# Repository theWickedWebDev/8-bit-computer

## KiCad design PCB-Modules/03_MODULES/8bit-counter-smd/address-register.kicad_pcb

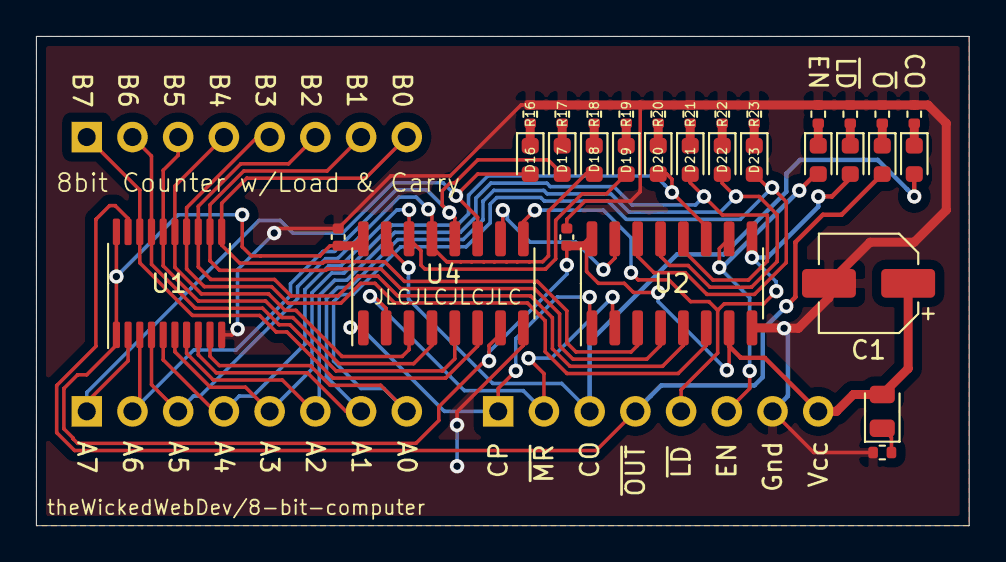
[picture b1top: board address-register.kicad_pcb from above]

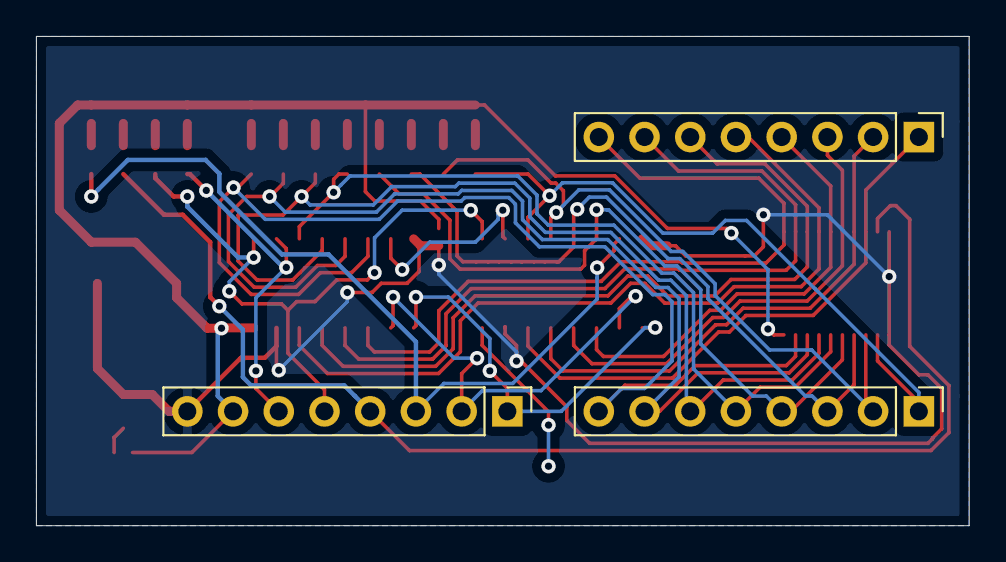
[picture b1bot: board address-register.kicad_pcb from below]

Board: 2 copper layers, 51.8 x 27.2 mm, 35 parts (3 on the bottom side), 38 nets.

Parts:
C1: SMD-ECAP-5x5.8; CP_Elec_5x5.8
C2, C5: CL05A106MQ5NUNC; C_0402_1005Metric
D2, D7, D12: 19-217/BHC-ZL1M2RY/3T; LED_0603_1608Metric
D6: NCD0805R1; LED_0805_2012Metric
D16, D17, D18, D19, D20, D21, D22, D23: 19-217/GHC-YR1S2/3T; LED_0603_1608Metric
J1, J2, J3: Conn_01x08; PinHeader_1x08_P2.54mm_Vertical
R2, R6, R7, R12, R14, R16, R17, R18, R19, R20, R21, R22, R23: 0402WGF1001TCE; R_0402_1005Metric
U1: 74HC245PW,118; TSSOP-20_4.4x6.5mm_P0.65mm
U2, U4: SN74HC161DR; SOIC-16_3.9x9.9mm_P1.27mm
U3: 19-213_Y2C-CQ2R2L_3T(CY); LED_0603_1608Metric

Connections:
BUS_00: J2.8, U1.11, U2.3
BUS_01: J2.7, U1.12, U2.4
BUS_02: J2.6, U1.13, U2.5
BUS_03: J2.5, U1.14, U2.6
BUS_04: J2.4, U1.15, U4.3
BUS_05: J2.3, U1.16, U4.4
BUS_06: J2.2, U1.17, U4.5
BUS_07: J2.1, U1.18, U4.6
CARRY_OUT: J1.3, U3.2, U4.15
CLOCK: J1.2, U2.2, U4.2
EN: D2.2, J1.6, U2.10
GND: C1.2, C2.2, C5.2, J1.7, R2.2, R6.2, R7.2, R12.2, R14.2, R16.2, R17.2, R18.2, R19.2, R20.2, R21.2, R22.2, R23.2, U1.10, U2.8, U4.8
unnamed: D2.1, R2.1
unnamed: D6.1, R6.1
unnamed: D7.1, R7.1
unnamed: D12.1, R12.1
unnamed: D16.1, R16.1
unnamed: D17.1, R17.1
unnamed: D18.1, R18.1
unnamed: D19.1, R19.1
unnamed: D20.1, R20.1
unnamed: D21.1, R21.1
unnamed: D22.1, R22.1
unnamed: D23.1, R23.1
unnamed: R14.1, U3.1
unnamed: U2.15, U4.10
Q0: D23.2, J3.8, U1.9, U2.14
Q1: D22.2, J3.7, U1.8, U2.13
Q2: D21.2, J3.6, U1.7, U2.12
Q3: D20.2, J3.5, U1.6, U2.11
Q4: D19.2, J3.4, U1.5, U4.14
Q5: D18.2, J3.3, U1.4, U4.13
Q6: D17.2, J3.2, U1.3, U4.12
Q7: D16.2, J3.1, U1.2, U4.11
VCC: C1.1, C2.1, C5.1, D6.2, J1.8, U1.1, U1.20, U2.7, U2.16, U4.7, U4.16
~LOAD: D7.2, J1.5, U2.9, U4.9
~OUT: D12.2, J1.4, U1.19
~RESET: J1.1, U2.1, U4.1

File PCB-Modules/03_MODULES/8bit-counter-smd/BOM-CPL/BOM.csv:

Designator,Value,LibPart,Footprint,Datasheet,C,Color,Description,JCLC,JLCPCB,NAME,,
C1,SMD-ECAP-5x5.8,Device:CP1_Small,Capacitor_SMD:CP_Elec_5x5.8,https://datasheet.lcsc.com/lcsc/1810010225_Lelon-VZS101M1ATR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,100µf,,"- - 5mm 100uF 10V -45℃~+105℃ ±20% 5.8mm 2000hrs 105℃ SMD,5x5.8mm Aluminum Electrolytic Capacitors - SMD ROHS",C140924,C140924,,,
C2,CL05A106MQ5NUNC,Device:C,Capacitor_SMD:C_0402_1005Metric,https://datasheet.lcsc.com/lcsc/1810191215_Samsung-Electro-M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,10µf,,X5R 6.3V ±20% 10uF 0402 Multilayer Ceramic Capacitors MLCC - SMD/SMT ROHS,C15525,C15525,,,
C5,CL05A106MQ5NUNC,Device:C,Capacitor_SMD:C_0402_1005Metric,https://datasheet.lcsc.com/lcsc/1810191215_Samsung-Electro-M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,10µf,,X5R 6.3V ±20% 10uF 0402 Multilayer Ceramic Capacitors MLCC - SMD/SMT ROHS,C15525,C15525,,,
D2,19-217/BHC-ZL1M2RY/3T,Device:LED,LED_SMD:LED_0603_1608Metric,https://datasheet.lcsc.com/lcsc/1811101510_Everlight-Elec-19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,,BLU,,C72041,C72041,,,
D6,NCD0805R1,Device:LED,LED_SMD:LED_0805_2012Metric,https://datasheet.lcsc.com/lcsc/2008201032_Foshan-NationStar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,,RED,,,C84256,,,
D7,19-217/BHC-ZL1M2RY/3T,Device:LED,LED_SMD:LED_0603_1608Metric,https://datasheet.lcsc.com/lcsc/1811101510_Everlight-Elec-19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,,BLU,,C72041,C72041,,,
D12,19-217/BHC-ZL1M2RY/3T,Device:LED,LED_SMD:LED_0603_1608Metric,https://datasheet.lcsc.com/lcsc/1811101510_Everlight-Elec-19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,,BLU,,C72041,C72041,,,
D16,19-217/GHC-YR1S2/3T,Device:LED,LED_SMD:LED_0603_1608Metric,https://datasheet.lcsc.com/lcsc/1811101510_Everlight-Elec-19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,,GRN,,C72043,C72043,,,
D17,19-217/GHC-YR1S2/3T,Device:LED,LED_SMD:LED_0603_1608Metric,https://datasheet.lcsc.com/lcsc/1811101510_Everlight-Elec-19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,,GRN,,C72043,C72043,,,
D18,19-217/GHC-YR1S2/3T,Device:LED,LED_SMD:LED_0603_1608Metric,https://datasheet.lcsc.com/lcsc/1811101510_Everlight-Elec-19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,,GRN,,C72043,C72043,,,
D19,19-217/GHC-YR1S2/3T,Device:LED,LED_SMD:LED_0603_1608Metric,https://datasheet.lcsc.com/lcsc/1811101510_Everlight-Elec-19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,,GRN,,C72043,C72043,,,
D20,19-217/GHC-YR1S2/3T,Device:LED,LED_SMD:LED_0603_1608Metric,https://datasheet.lcsc.com/lcsc/1811101510_Everlight-Elec-19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,,GRN,,C72043,C72043,,,
D21,19-217/GHC-YR1S2/3T,Device:LED,LED_SMD:LED_0603_1608Metric,https://datasheet.lcsc.com/lcsc/1811101510_Everlight-Elec-19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,,GRN,,C72043,C72043,,,
D22,19-217/GHC-YR1S2/3T,Device:LED,LED_SMD:LED_0603_1608Metric,https://datasheet.lcsc.com/lcsc/1811101510_Everlight-Elec-19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,,GRN,,C72043,C72043,,,
D23,19-217/GHC-YR1S2/3T,Device:LED,LED_SMD:LED_0603_1608Metric,https://datasheet.lcsc.com/lcsc/1811101510_Everlight-Elec-19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,,GRN,,C72043,C72043,,,
J1,Conn_01x08,Connector_Generic:Conn_01x08,Connector_PinHeader_2.54mm:PinHeader_1x08_P2.54mm_Vertical,~,,,,,,,,
J2,Conn_01x08,Connector_Generic:Conn_01x08,Connector_PinHeader_2.54mm:PinHeader_1x08_P2.54mm_Vertical,~,,,,,,,,
J3,Conn_01x08,Connector_Generic:Conn_01x08,Connector_PinHeader_2.54mm:PinHeader_1x08_P2.54mm_Vertical,~,,,,,,,,
R2,0402WGF1001TCE,Device:R_Small_US,Resistor_SMD:R_0402_1005Metric,https://datasheet.lcsc.com/lcsc/1811132311_UNI-ROYAL-Uniroya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,,,±1% 1/16W ±100ppm/℃ 1kΩ 0402 Chip Resistor - Surface Mount ROHS,C11702,C11702,,,
R6,0402WGF1001TCE,Device:R_Small_US,Resistor_SMD:R_0402_1005Metric,https://datasheet.lcsc.com/lcsc/1811132311_UNI-ROYAL-Uniroya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,,,±1% 1/16W ±100ppm/℃ 1kΩ 0402 Chip Resistor - Surface Mount ROHS,,C11702,,,
R7,0402WGF1001TCE,Device:R_Small_US,Resistor_SMD:R_0402_1005Metric,https://datasheet.lcsc.com/lcsc/1811132311_UNI-ROYAL-Uniroya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,,,±1% 1/16W ±100ppm/℃ 1kΩ 0402 Chip Resistor - Surface Mount ROHS,C11702,C11702,,,
R12,0402WGF1001TCE,Device:R_Small_US,Resistor_SMD:R_0402_1005Metric,https://datasheet.lcsc.com/lcsc/1811132311_UNI-ROYAL-Uniroya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,,,±1% 1/16W ±100ppm/℃ 1kΩ 0402 Chip Resistor - Surface Mount ROHS,C11702,C11702,,,
R14,0402WGF1001TCE,Device:R_Small_US,Resistor_SMD:R_0402_1005Metric,https://datasheet.lcsc.com/lcsc/1811132311_UNI-ROYAL-Uniroya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,,,±1% 1/16W ±100ppm/℃ 1kΩ 0402 Chip Resistor - Surface Mount ROHS,,C11702,,,
R16,0402WGF1001TCE,Device:R_Small_US,Resistor_SMD:R_0402_1005Metric,https://datasheet.lcsc.com/lcsc/1811132311_UNI-ROYAL-Uniroya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,,,±1% 1/16W ±100ppm/℃ 1kΩ 0402 Chip Resistor - Surface Mount ROHS,C11702,C11702,,,
R17,0402WGF1001TCE,Device:R_Small_US,Resistor_SMD:R_0402_1005Metric,https://datasheet.lcsc.com/lcsc/1811132311_UNI-ROYAL-Uniroya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,,,±1% 1/16W ±100ppm/℃ 1kΩ 0402 Chip Resistor - Surface Mount ROHS,C11702,C11702,,,
R18,0402WGF1001TCE,Device:R_Small_US,Resistor_SMD:R_0402_1005Metric,https://datasheet.lcsc.com/lcsc/1811132311_UNI-ROYAL-Uniroya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,,,±1% 1/16W ±100ppm/℃ 1kΩ 0402 Chip Resistor - Surface Mount ROHS,C11702,C11702,,,
R19,0402WGF1001TCE,Device:R_Small_US,Resistor_SMD:R_0402_1005Metric,https://datasheet.lcsc.com/lcsc/1811132311_UNI-ROYAL-Uniroya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,,,±1% 1/16W ±100ppm/℃ 1kΩ 0402 Chip Resistor - Surface Mount ROHS,C11702,C11702,,,
R20,0402WGF1001TCE,Device:R_Small_US,Resistor_SMD:R_0402_1005Metric,https://datasheet.lcsc.com/lcsc/1811132311_UNI-ROYAL-Uniroya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,,,±1% 1/16W ±100ppm/℃ 1kΩ 0402 Chip Resistor - Surface Mount ROHS,C11702,C11702,,,
R21,0402WGF1001TCE,Device:R_Small_US,Resistor_SMD:R_0402_1005Metric,https://datasheet.lcsc.com/lcsc/1811132311_UNI-ROYAL-Uniroya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,,,±1% 1/16W ±100ppm/℃ 1kΩ 0402 Chip Resistor - Surface Mount ROHS,C11702,C11702,,,
R22,0402WGF1001TCE,Device:R_Small_US,Resistor_SMD:R_0402_1005Metric,https://datasheet.lcsc.com/lcsc/1811132311_UNI-ROYAL-Uniroya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,,,±1% 1/16W ±100ppm/℃ 1kΩ 0402 Chip Resistor - Surface Mount ROHS,C11702,C11702,,,
R23,0402WGF1001TCE,Device:R_Small_US,Resistor_SMD:R_0402_1005Metric,https://datasheet.lcsc.com/lcsc/1811132311_UNI-ROYAL-Uniroya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,,,±1% 1/16W ±100ppm/℃ 1kΩ 0402 Chip Resistor - Surface Mount ROHS,C11702,C11702,,,
U1,"74HC245PW,118","JLCPCB:74HC245PW,118",Package_SO:TSSOP-20_4.4x6.5mm_P0.65mm,http://www.ti.com/lit/gpn/sn74LS245,,,,C5626,,,,
U2,SN74HC161DR,JLCPCB:SN74HC161DR,Package_SO:SOIC-16_3.9x9.9mm_P1.27mm,https://datasheet.lcsc.com/lcsc/1809051912_Texas-Instruments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,,,Binary Counter - SOIC-16_150mil 74 Series ROHS,C6824,,74HC161,,
U3,19-213_Y2C-CQ2R2L_3T(CY),JLCPCB:19-213_Y2C-CQ2R2L_3T(CY),LED_SMD:LED_0603_1608Metric,,,YLW,Yellow 585.5~591.5nm 0603 Light Emitting Diodes (LED) ROHS,C72038,,,,
U4,SN74HC161DR,JLCPCB:SN74HC161DR,Package_SO:SOIC-16_3.9x9.9mm_P1.27mm,https://datasheet.lcsc.com/lcsc/1809051912_Texas-Instruments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,,,Binary Counter - SOIC-16_150mil 74 Series ROHS,C6824,,74HC161,,

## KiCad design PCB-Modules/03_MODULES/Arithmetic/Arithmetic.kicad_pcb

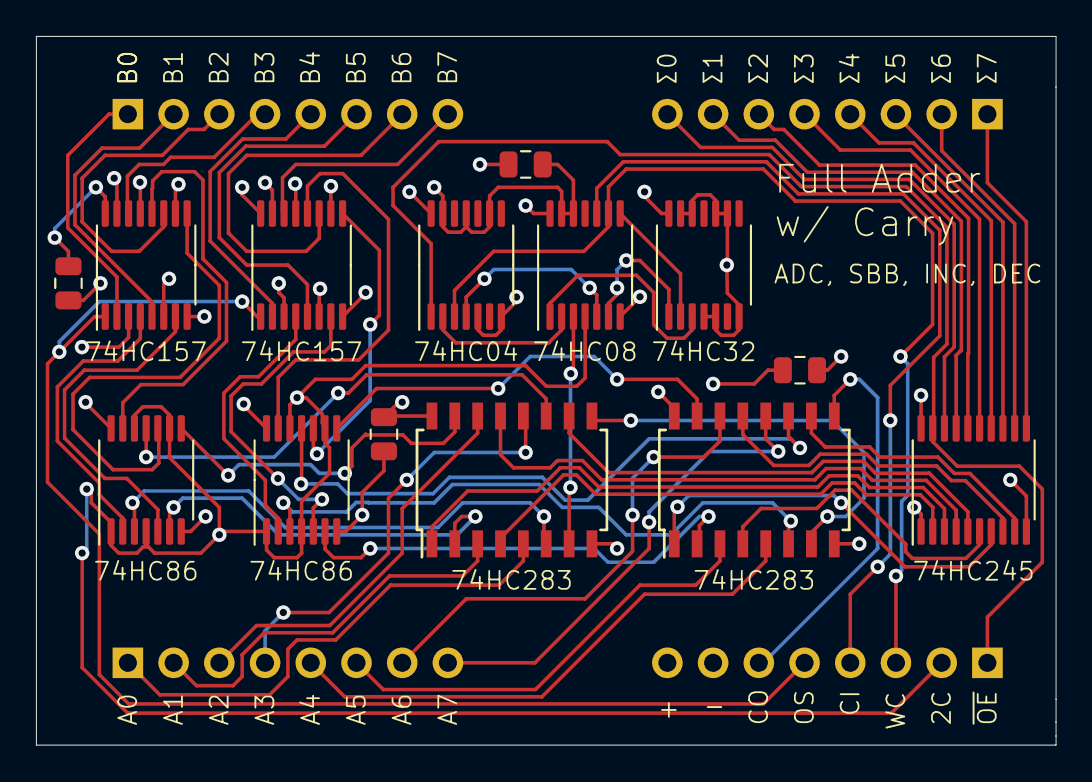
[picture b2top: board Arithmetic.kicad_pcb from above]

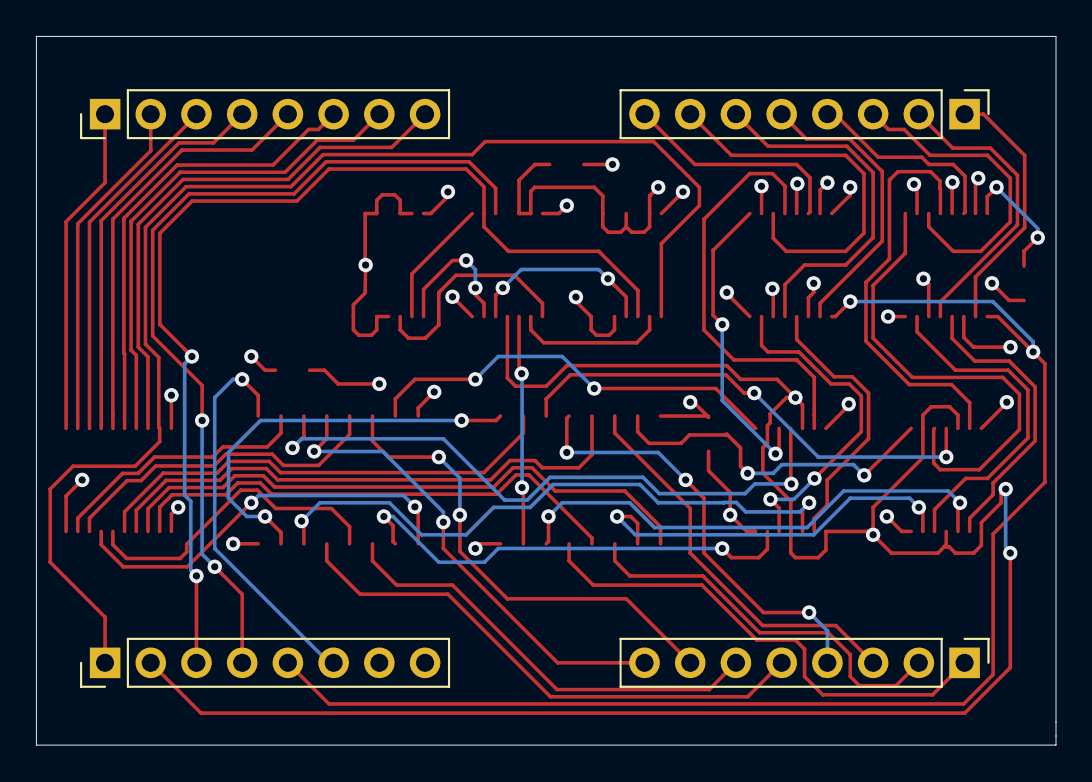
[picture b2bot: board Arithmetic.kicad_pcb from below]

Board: 4 copper layers, 56.6 x 39.4 mm, 18 parts (4 on the bottom side), 63 nets.

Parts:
C1, C2, C3, C4: C; C_0805_2012Metric
J1, J2, J3, J4: Conn_01x08; PinHeader_1x08_P2.54mm_Vertical
U1, U2: 74LS157; TSSOP-16_4.4x5mm_P0.65mm
U3, U4: 74LS86; TSSOP-14_4.4x5mm_P0.65mm
U5, U6: 74LS283; SOIC-16W_5.3x10.2mm_P1.27mm
U7: 74LS245; TSSOP-20_4.4x6.5mm_P0.65mm
U32: 74LS04; TSSOP-14_4.4x5mm_P0.65mm
U33: 74LS08; TSSOP-14_4.4x5mm_P0.65mm
U34: 74LS32; TSSOP-14_4.4x5mm_P0.65mm

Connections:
A0: J1.1, U5.5
A1: J1.2, U5.3
A2: J1.3, U5.14
A3: J1.4, U5.12
A4: J1.5, U6.5
A5: J1.6, U6.3
A6: J1.7, U6.14
A7: J1.8, U6.12
ADC_SBB: J4.3, U32.3, U33.9
ADDER_CARRY_IN: U5.7, U33.3
ADDER_CARRY_OUT: J4.6, U6.9
B0: J2.1, U1.2
B1: J2.2, U1.5
B2: J2.3, U1.11
B3: J2.4, U1.14
B4: J2.5, U2.2
B5: J2.6, U2.5
B6: J2.7, U2.11
B7: J2.8, U2.14
CARRY_FLAG_IN: J4.4, U33.10
GND: C1.2, C2.2, C3.2, C4.2, J4.7, U1.8, U1.15, U2.8, U2.15, U3.7, U4.7, U5.8, U6.8, U7.10, U32.5, U32.7, U32.9, U32.11, U32.13, U33.7, U33.12, U33.13, U34.4, U34.5, U34.7, U34.9, U34.10, U34.12, U34.13
unnamed: U1.4, U3.2
unnamed: U1.7, U3.5
unnamed: U1.9, U3.10
unnamed: U1.12, U3.13
unnamed: U2.4, U4.2
unnamed: U2.7, U4.5
unnamed: U2.9, U4.10
unnamed: U2.12, U4.13
unnamed: U5.1, U7.3
unnamed: U5.4, U7.2
unnamed: U5.9, U6.7
unnamed: U5.10, U7.5
unnamed: U5.13, U7.4
unnamed: U6.1, U7.7
unnamed: U6.4, U7.6
unnamed: U6.10, U7.9
unnamed: U6.13, U7.8
unnamed: U32.2, U33.2
unnamed: U32.4, U33.5
unnamed: U33.1, U34.3
unnamed: U33.6, U34.1
unnamed: U33.8, U34.2
OP0: U3.3, U5.6
OP1: U3.6, U5.2
OP2: U3.8, U5.15
OP3: U3.11, U5.11
OP4: U4.3, U6.6
OP5: U4.6, U6.2
OP6: U4.8, U6.15
OP7: U4.11, U6.11
OP_MUX_SEL: J4.5, U1.1, U2.1
SUM0: J3.8, U7.18
SUM1: J3.7, U7.17
SUM2: J3.6, U7.16
SUM3: J3.5, U7.15
SUM4: J3.4, U7.14
SUM5: J3.3, U7.13
SUM6: J3.2, U7.12
SUM7: J3.1, U7.11
TWOS_COMP: J4.2, U3.1, U3.4, U3.9, U3.12, U4.1, U4.4, U4.9, U4.12, U33.4
VCC: C1.1, C2.1, C3.1, C4.1, J4.8, U1.3, U1.6, U1.10, U1.13, U1.16, U2.3, U2.6, U2.10, U2.13, U2.16, U3.14, U4.14, U5.16, U6.16, U7.1, U7.20, U32.14, U33.14, U34.14
~ADDER_OUT: J4.1, U7.19, U32.1

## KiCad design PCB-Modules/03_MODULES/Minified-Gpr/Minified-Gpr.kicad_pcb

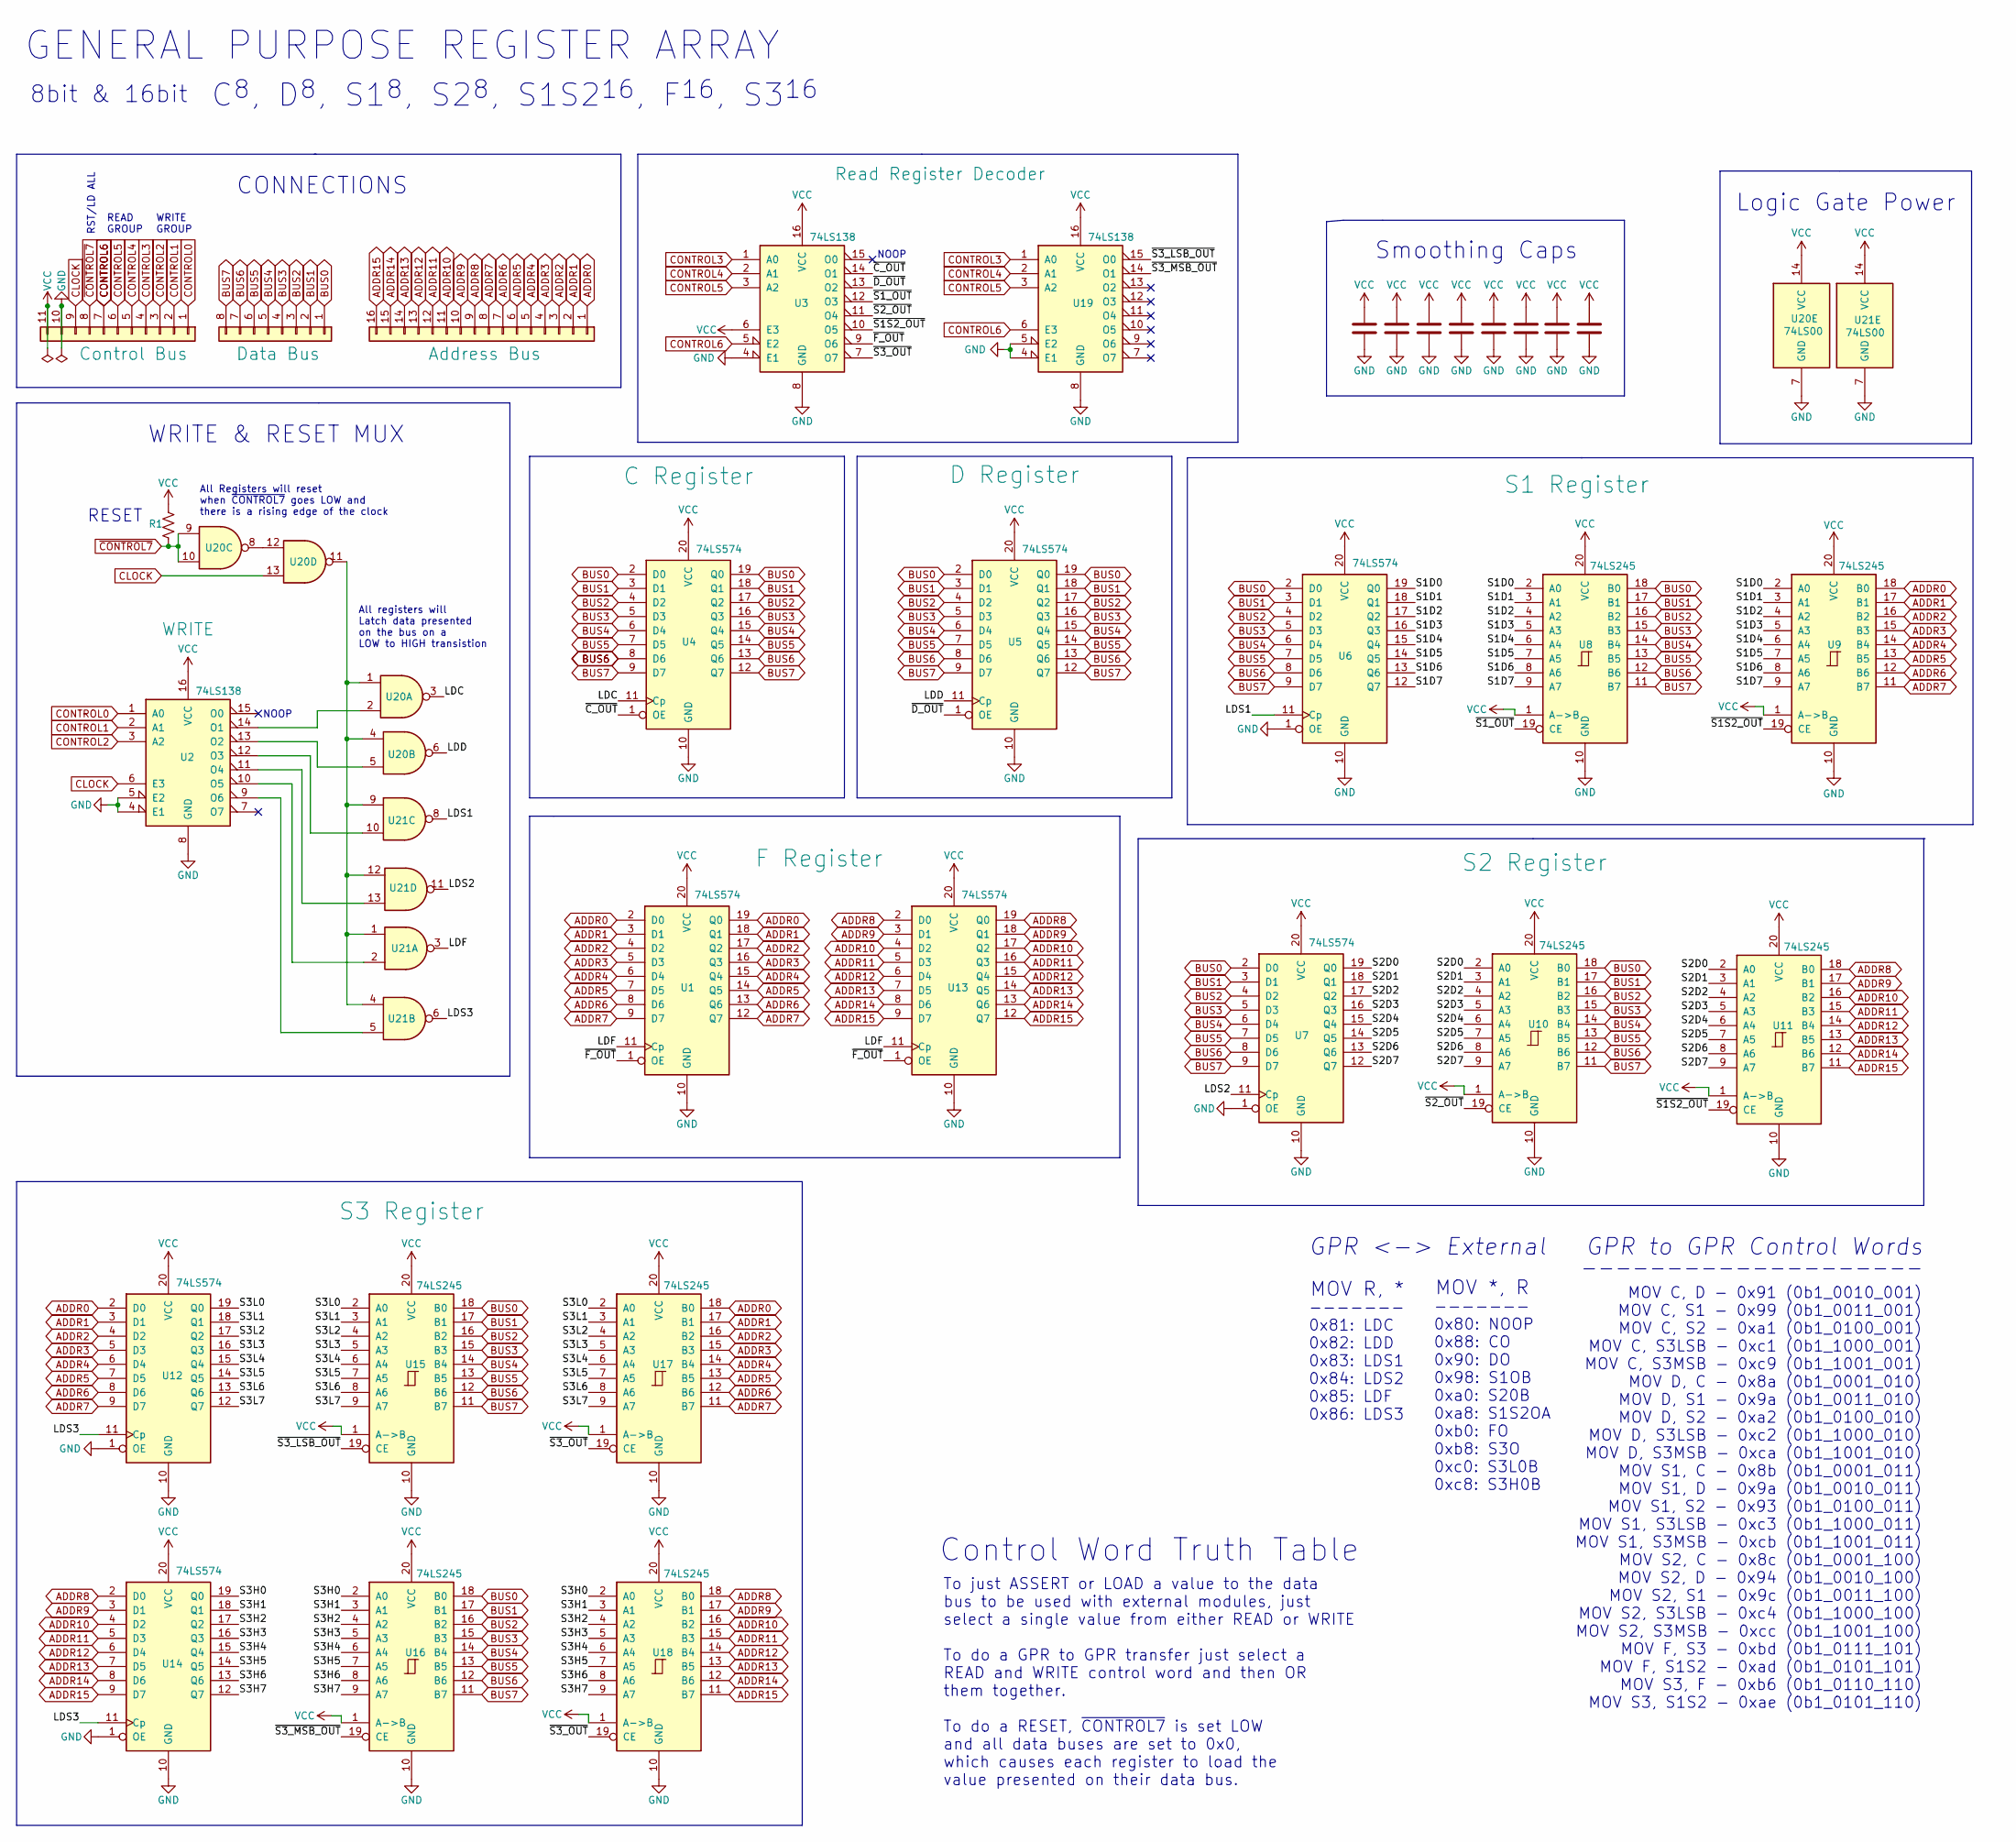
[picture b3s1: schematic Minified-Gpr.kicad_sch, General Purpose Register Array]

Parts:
C1, C2, C3, C4, C5, C6, C7, C8: C; C_0805_2012Metric
J1: Conn_01x08; PinHeader_1x08_P2.54mm_Vertical
J2: Conn_01x16; PinHeader_1x16_P2.54mm_Vertical
J3: Conn_01x11; PinHeader_1x11_P2.54mm_Vertical
R1: R_US; R_0805_2012Metric
U1, U4, U5, U6, U7, U12, U13, U14: 74LS574; SO-20_5.3x12.6mm_P1.27mm
U2, U3, U19: 74LS138; TSSOP-16_4.4x5mm_P0.65mm
U8, U9, U10, U11, U15, U16, U17, U18: 74LS245; TSSOP-20_4.4x6.5mm_P0.65mm
U20, U21: 74LS00; TSSOP-14_4.4x5mm_P0.65mm

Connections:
/LDC: U4.11 (Cp), U20.3
/LDD: U5.11 (Cp), U20.6
/LDF: U1.11 (Cp), U13.11 (Cp), U21.3
/LDS1: U6.11 (Cp), U21.8
/LDS2: U7.11 (Cp), U21.11
/LDS3: U12.11 (Cp), U14.11 (Cp), U21.6
/S1D0: U6.19 (Q0), U8.2 (A0), U9.2 (A0)
/S1D1: U6.18 (Q1), U8.3 (A1), U9.3 (A1)
/S1D2: U6.17 (Q2), U8.4 (A2), U9.4 (A2)
/S1D3: U6.16 (Q3), U8.5 (A3), U9.5 (A3)
/S1D4: U6.15 (Q4), U8.6 (A4), U9.6 (A4)
/S1D5: U6.14 (Q5), U8.7 (A5), U9.7 (A5)
/S1D6: U6.13 (Q6), U8.8 (A6), U9.8 (A6)
/S1D7: U6.12 (Q7), U8.9 (A7), U9.9 (A7)
/S2D0: U7.19 (Q0), U10.2 (A0), U11.2 (A0)
/S2D1: U7.18 (Q1), U10.3 (A1), U11.3 (A1)
/S2D2: U7.17 (Q2), U10.4 (A2), U11.4 (A2)
/S2D3: U7.16 (Q3), U10.5 (A3), U11.5 (A3)
/S2D4: U7.15 (Q4), U10.6 (A4), U11.6 (A4)
/S2D5: U7.14 (Q5), U10.7 (A5), U11.7 (A5)
/S2D6: U7.13 (Q6), U10.8 (A6), U11.8 (A6)
/S2D7: U7.12 (Q7), U10.9 (A7), U11.9 (A7)
/S3H0: U14.19 (Q0), U16.2 (A0), U18.2 (A0)
/S3H1: U14.18 (Q1), U16.3 (A1), U18.3 (A1)
/S3H2: U14.17 (Q2), U16.4 (A2), U18.4 (A2)
/S3H3: U14.16 (Q3), U16.5 (A3), U18.5 (A3)
/S3H4: U14.15 (Q4), U16.6 (A4), U18.6 (A4)
/S3H5: U14.14 (Q5), U16.7 (A5), U18.7 (A5)
/S3H6: U14.13 (Q6), U16.8 (A6), U18.8 (A6)
/S3H7: U14.12 (Q7), U16.9 (A7), U18.9 (A7)
/S3L0: U12.19 (Q0), U15.2 (A0), U17.2 (A0)
/S3L1: U12.18 (Q1), U15.3 (A1), U17.3 (A1)
/S3L2: U12.17 (Q2), U15.4 (A2), U17.4 (A2)
/S3L3: U12.16 (Q3), U15.5 (A3), U17.5 (A3)
/S3L4: U12.15 (Q4), U15.6 (A4), U17.6 (A4)
/S3L5: U12.14 (Q5), U15.7 (A5), U17.7 (A5)
/S3L6: U12.13 (Q6), U15.8 (A6), U17.8 (A6)
/S3L7: U12.12 (Q7), U15.9 (A7), U17.9 (A7)
/~C_OUT: U3.14 (O1), U4.1 (OE)
/~D_OUT: U3.13 (O2), U5.1 (OE)
/~F_OUT: U1.1 (OE), U3.9 (O6), U13.1 (OE)
/~S1S2_OUT: U3.10 (O5), U9.19 (CE), U11.19 (CE)
/~S1_OUT: U3.12 (O3), U8.19 (CE)
/~S2_OUT: U3.11 (O4), U10.19 (CE)
/~S3_LSB_OUT: U15.19 (CE), U19.15 (O0)
/~S3_MSB_OUT: U16.19 (CE), U19.14 (O1)
/~S3_OUT: U3.7 (O7), U17.19 (CE), U18.19 (CE)
ADDR0: J2.1, U1.2 (D0), U1.19 (Q0), U9.18 (B0), U12.2 (D0), U17.18 (B0)
ADDR1: J2.2, U1.3 (D1), U1.18 (Q1), U9.17 (B1), U12.3 (D1), U17.17 (B1)
ADDR2: J2.3, U1.4 (D2), U1.17 (Q2), U9.16 (B2), U12.4 (D2), U17.16 (B2)
ADDR3: J2.4, U1.5 (D3), U1.16 (Q3), U9.15 (B3), U12.5 (D3), U17.15 (B3)
ADDR4: J2.5, U1.6 (D4), U1.15 (Q4), U9.14 (B4), U12.6 (D4), U17.14 (B4)
ADDR5: J2.6, U1.7 (D5), U1.14 (Q5), U9.13 (B5), U12.7 (D5), U17.13 (B5)
ADDR6: J2.7, U1.8 (D6), U1.13 (Q6), U9.12 (B6), U12.8 (D6), U17.12 (B6)
ADDR7: J2.8, U1.9 (D7), U1.12 (Q7), U9.11 (B7), U12.9 (D7), U17.11 (B7)
ADDR8: J2.9, U11.18 (B0), U13.2 (D0), U13.19 (Q0), U14.2 (D0), U18.18 (B0)
ADDR9: J2.10, U11.17 (B1), U13.3 (D1), U13.18 (Q1), U14.3 (D1), U18.17 (B1)
ADDR10: J2.11, U11.16 (B2), U13.4 (D2), U13.17 (Q2), U14.4 (D2), U18.16 (B2)
ADDR11: J2.12, U11.15 (B3), U13.5 (D3), U13.16 (Q3), U14.5 (D3), U18.15 (B3)
ADDR12: J2.13, U11.14 (B4), U13.6 (D4), U13.15 (Q4), U14.6 (D4), U18.14 (B4)
ADDR13: J2.14, U11.13 (B5), U13.7 (D5), U13.14 (Q5), U14.7 (D5), U18.13 (B5)
ADDR14: J2.15, U11.12 (B6), U13.8 (D6), U13.13 (Q6), U14.8 (D6), U18.12 (B6)
ADDR15: J2.16, U11.11 (B7), U13.9 (D7), U13.12 (Q7), U14.9 (D7), U18.11 (B7)
BUS0: J1.1, U4.2 (D0), U4.19 (Q0), U5.2 (D0), U5.19 (Q0), U6.2 (D0), U7.2 (D0), U8.18 (B0), U10.18 (B0), U15.18 (B0), U16.18 (B0)
BUS1: J1.2, U4.3 (D1), U4.18 (Q1), U5.3 (D1), U5.18 (Q1), U6.3 (D1), U7.3 (D1), U8.17 (B1), U10.17 (B1), U15.17 (B1), U16.17 (B1)
BUS2: J1.3, U4.4 (D2), U4.17 (Q2), U5.4 (D2), U5.17 (Q2), U6.4 (D2), U7.4 (D2), U8.16 (B2), U10.16 (B2), U15.16 (B2), U16.16 (B2)
BUS3: J1.4, U4.5 (D3), U4.16 (Q3), U5.5 (D3), U5.16 (Q3), U6.5 (D3), U7.5 (D3), U8.15 (B3), U10.15 (B3), U15.15 (B3), U16.15 (B3)
BUS4: J1.5, U4.6 (D4), U4.15 (Q4), U5.6 (D4), U5.15 (Q4), U6.6 (D4), U7.6 (D4), U8.14 (B4), U10.14 (B4), U15.14 (B4), U16.14 (B4)
BUS5: J1.6, U4.7 (D5), U4.14 (Q5), U5.7 (D5), U5.14 (Q5), U6.7 (D5), U7.7 (D5), U8.13 (B5), U10.13 (B5), U15.13 (B5), U16.13 (B5)
BUS6: J1.7, U4.8 (D6), U4.13 (Q6), U5.8 (D6), U5.13 (Q6), U6.8 (D6), U7.8 (D6), U8.12 (B6), U10.12 (B6), U15.12 (B6), U16.12 (B6)
BUS7: J1.8, U4.9 (D7), U4.12 (Q7), U5.9 (D7), U5.12 (Q7), U6.9 (D7), U7.9 (D7), U8.11 (B7), U10.11 (B7), U15.11 (B7), U16.11 (B7)
CLOCK: J3.9, U2.6 (E3), U20.13
CONTROL0: J3.1, U2.1 (A0)
CONTROL1: J3.2, U2.2 (A1)
CONTROL2: J3.3, U2.3 (A2)
CONTROL3: J3.4, U3.1 (A0), U19.1 (A0)
CONTROL4: J3.5, U3.2 (A1), U19.2 (A1)
CONTROL5: J3.6, U3.3 (A2), U19.3 (A2)
CONTROL6: J3.7, U3.5 (E2), U19.6 (E3)
GND: C1.2, C2.2, C3.2, C4.2, C5.2, C6.2, C7.2, C8.2, J3.10, U1.10 (GND), U2.4 (E1), U2.5 (E2), U2.8 (GND), U3.4 (E1), U3.8 (GND), U4.10 (GND), U5.10 (GND), U6.1 (OE), U6.10 (GND), U7.1 (OE), U7.10 (GND), U8.10 (GND), U9.10 (GND), U10.10 (GND), U11.10 (GND), U12.1 (OE), U12.10 (GND), U13.10 (GND), U14.1 (OE), U14.10 (GND), U15.10 (GND), U16.10 (GND), U17.10 (GND), U18.10 (GND), U19.4 (E1), U19.5 (E2), U19.8 (GND), U20.7 (GND), U21.7 (GND)
unnamed: U2.9 (O6), U21.5
unnamed: U2.10 (O5), U21.2
unnamed: U2.11 (O4), U21.13
unnamed: U2.12 (O3), U21.10
unnamed: U2.13 (O2), U20.5
unnamed: U2.14 (O1), U20.2
unnamed: U20.1, U20.4, U20.11, U21.1, U21.4, U21.9, U21.12
unnamed: U20.8, U20.12
VCC: C1.1, C2.1, C3.1, C4.1, C5.1, C6.1, C7.1, C8.1, J3.11, R1.2, U1.20 (VCC), U2.16 (VCC), U3.6 (E3), U3.16 (VCC), U4.20 (VCC), U5.20 (VCC), U6.20 (VCC), U7.20 (VCC), U8.1 (A->B), U8.20 (VCC), U9.1 (A->B), U9.20 (VCC), U10.1 (A->B), U10.20 (VCC), U11.1 (A->B), U11.20 (VCC), U12.20 (VCC), U13.20 (VCC), U14.20 (VCC), U15.1 (A->B), U15.20 (VCC), U16.1 (A->B), U16.20 (VCC), U17.1 (A->B), U17.20 (VCC), U18.1 (A->B), U18.20 (VCC), U19.16 (VCC), U20.14 (VCC), U21.14 (VCC)
~CONTROL7: J3.8, R1.1, U20.9, U20.10

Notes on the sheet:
WRITE & RESET MUX
GPR <-> External
------- 0x81: LDC 0x82: LDD 0x83: LDS1 0x84: LDS2 0x85: LDF 0x86: LDS3
RESET
MOV R, *
GPR to GPR Control Words
READ GROUP
MOV *, R
To just ASSERT or LOAD a value to the data bus to be used with external modules, just select a single value from either READ or WRITE To do a GPR to GPR transfer just select a READ and WRITE control word and then OR them together. To do a RESET, ~{CONTROL7} is set LOW and all data buses are set to 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
Control Word Truth Table
All registers will Latch data presented on the bus on a LOW to HIGH transistion
NOOP
8bit & 16bit
CONNECTIONS
Smoothing Caps
GENERAL PURPOSE REGISTER ARRAY
------- 0x80: NOOP 0x88: CO 0x90: DO 0x98: S1OB 0xa0: S20B 0xa8: S1S2OA 0xb0: FO 0xb8: S3O 0xc0: S3L0B 0xc8: S3H0B
All Registers will reset when ~{CONTROL7} goes LOW and there is a rising edge of the clock
--------------------
Logic Gate Power
C^{8}, D^{8}, S1^{8}, S2^{8}, S1S2^{16}, F^{16}, S3^{16}
WRITE GROUP
RST/LD ALL
MOV C, D - 0x91 (0b1_0010_001) MOV C, S1 - 0x99 (0b1_0011_001) MOV C, S2 - 0xa1 (0b1_0100_001) MOV C, S3LSB - 0xc1 (0b1_1000_001) MOV C, S3MSB - 0xc9 (0b1_1001_001) MOV D, C - 0x8a (0b1_0001_010) MOV D, S1 - 0x9a (0b1_0011_010) MOV D, S2 - 0xa2 (0b1_0100_010) MOV D, S3LSB - 0xc2 (0b1_1000_010) MOV 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

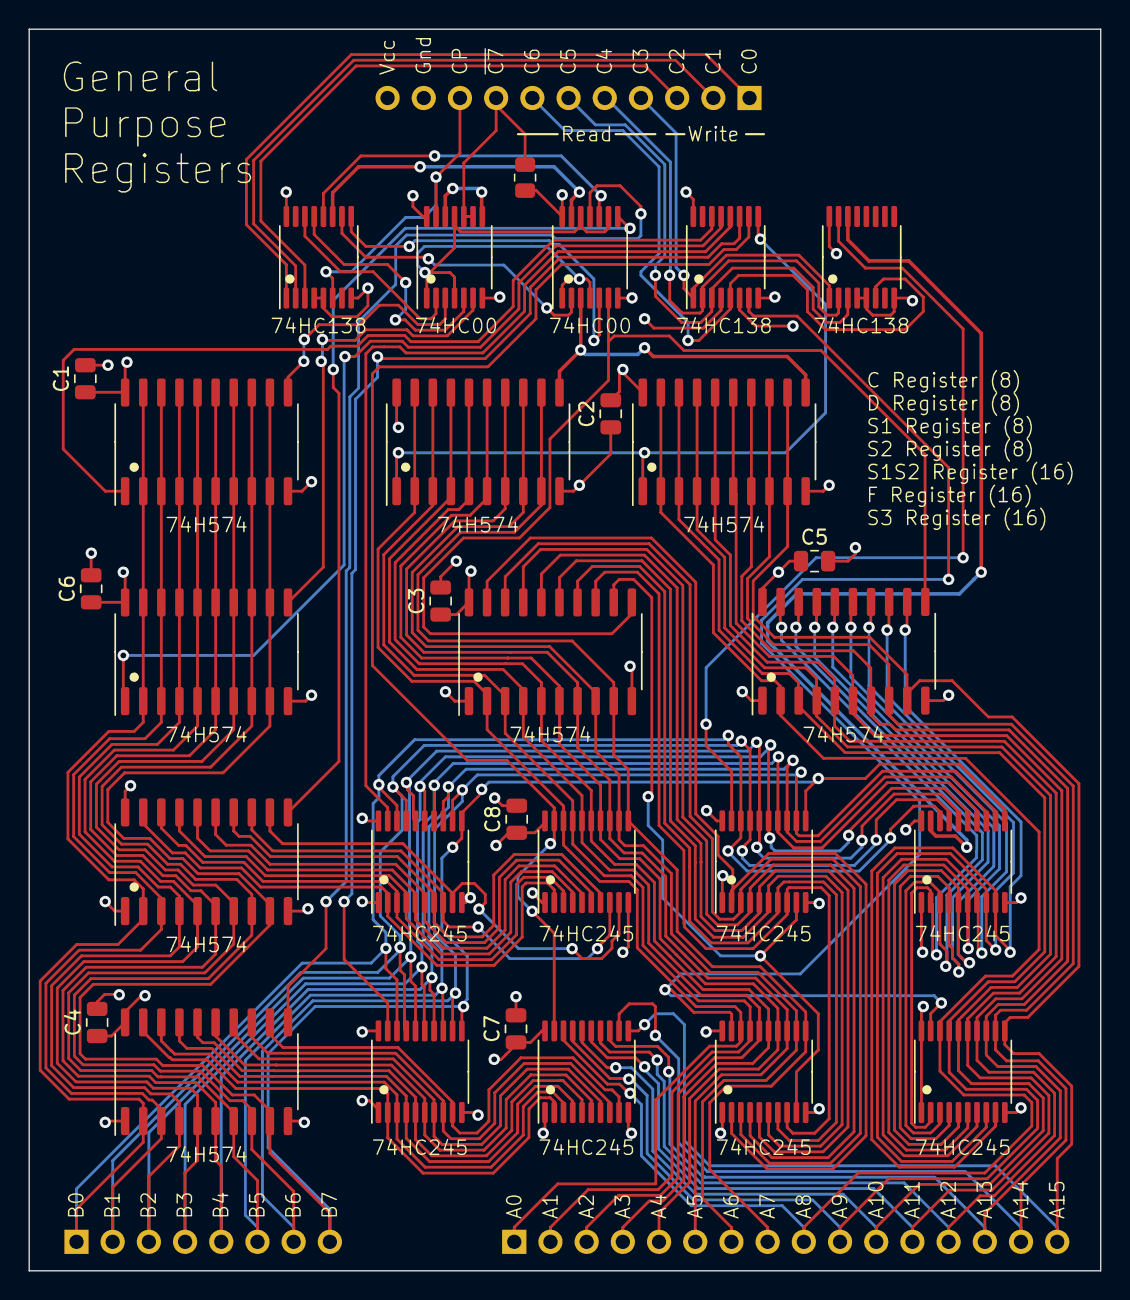
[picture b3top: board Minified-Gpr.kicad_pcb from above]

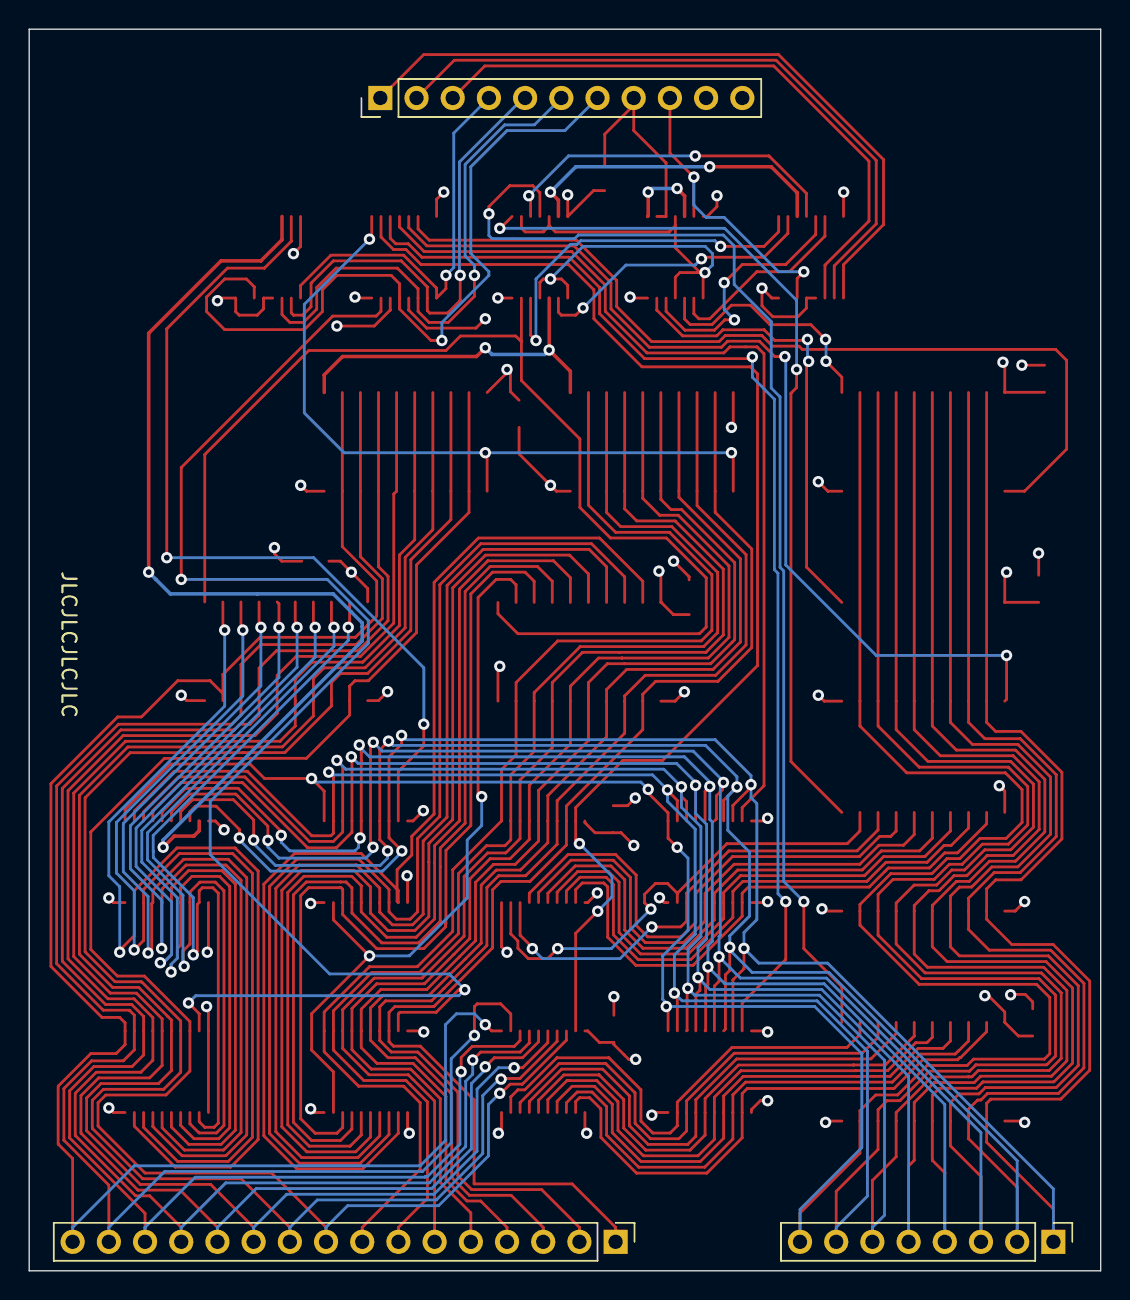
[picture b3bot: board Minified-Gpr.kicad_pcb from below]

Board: 4 copper layers, 75.2 x 87.1 mm, 33 parts (3 on the bottom side), 90 nets.
